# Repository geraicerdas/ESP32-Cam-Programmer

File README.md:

### Repository Content
* **/hardware** : Schematic files (.pdf) some of older version included Eagle design files (.sch and .brd)
* **/production** : gerber file for pcb manufacturing

You can purchase this product from  

# ESP32-Cam-Programmer
This is external programming for ESP32-Cam that you can simple attach it for easy upload your code to ESP32-Cam. Keep the slide switch at 3.3V so it is not harmful for your ESP32-Cam. ESP32-Cam programmer also have a breakout pins that makes it easier for you to connect the I/O pins of the ESP32-Cam to other circuits (no need breadboard). Not only for ESP32-Cam, you can use this board to program another MCU's like Arduino Pro mini that need USB to Serial Converter

The latest version have several changes :
- Added a 3V3 Voltage Regulator
- Added voltage selector switch (5V or 3.3V compatible)
- Compatible with both older or newer ESP32-Cam
- changes PCB shape and color

If you want to make your self, just download the gerber file in production folder. Send it to your fav pcb manufacturer. And dont forget to get the Bill of materials :
|Qty | Part Name | Parts | MPN |
| ------------- |:-------------|:-------------| -----:|
| 2 | Female Header 8P 2.54mm pitch | J5 | X6511FV-08-C85D32 |
| 2 | Male Header 8P 2.54mm pitch | J2, J3 | X4611WRS-08I-C40D28 |
| 1 | USB type C Connector 16P | J4 | U262-161N-4BVC11 |
| 1 | CH340G/CH340C | U1 | CH340G |
| 1 | SMD Resonator 12MHz CSTCE | X1 | CSTCE12M0G15C99-R0 |
| 1 | AP2112K-3.3TRG1 | U2 | AP2112K-3.3TRG1 |
| 1 | Chip Resistor 0 0805 | R10, R11 | 0805W8F0000T5E |
| 3 | Chip Resistor 1K 0603 | R4, R6, R7 | 0603WAF1001T5E |
| 3 | Chip Resistor 10K 0603 | R1, R2, R3 | 0603WAF1002T5E |
| 2 | Chip Resistor 4K7 0603 | R8, R9 | 0603WAF4701T5E |
| 5 | Chip Capacitor 100nF 0603 | C3, C5, C6, C8, C21 | CL10B104KB8NNNC |
| 3 | Chip Capacitor 10uF 0603 | C2, C4, C7 | CL10A106KP8NNNC |
| 1 | N-Channel MOSFET AO3400 | Q1 | AO3400 |
| 2 | Transistor S8050 | Q2, Q3 | S8050 |
| 2 | Slide Switch AYZ0202W | SW | SS-3390S-L2 |
| 2 | Push Button YD3414 | S1, S2 | TS-1186U-B-A |
| 2 | SMD LED 0805 Red | RX, TX | 17-21/R6C-AQ2R2B/3T |
| 1 | SMD LED 0805 Green | PWR | 17-21/GHC-YR1S2/3T |
| 1 | Schottky Diode 1N5819HW | D1 | 1N5819WS |

Below is the first version of ESP32-Cam Programmer. We keep this for your references.

## License
*We invests time and resources providing this open-source hardware, please support us by purchasing our products.*

*Designed by **[Insan Sains](https://www.youtube.com/insansains)** for **[Gerai Cerdas](https://geraicerdas.com)**, with contributions from the open source community. Creative Commons Attribution/Share-Alike, all text above must be included in any redistribution. See license.txt for additional information.*

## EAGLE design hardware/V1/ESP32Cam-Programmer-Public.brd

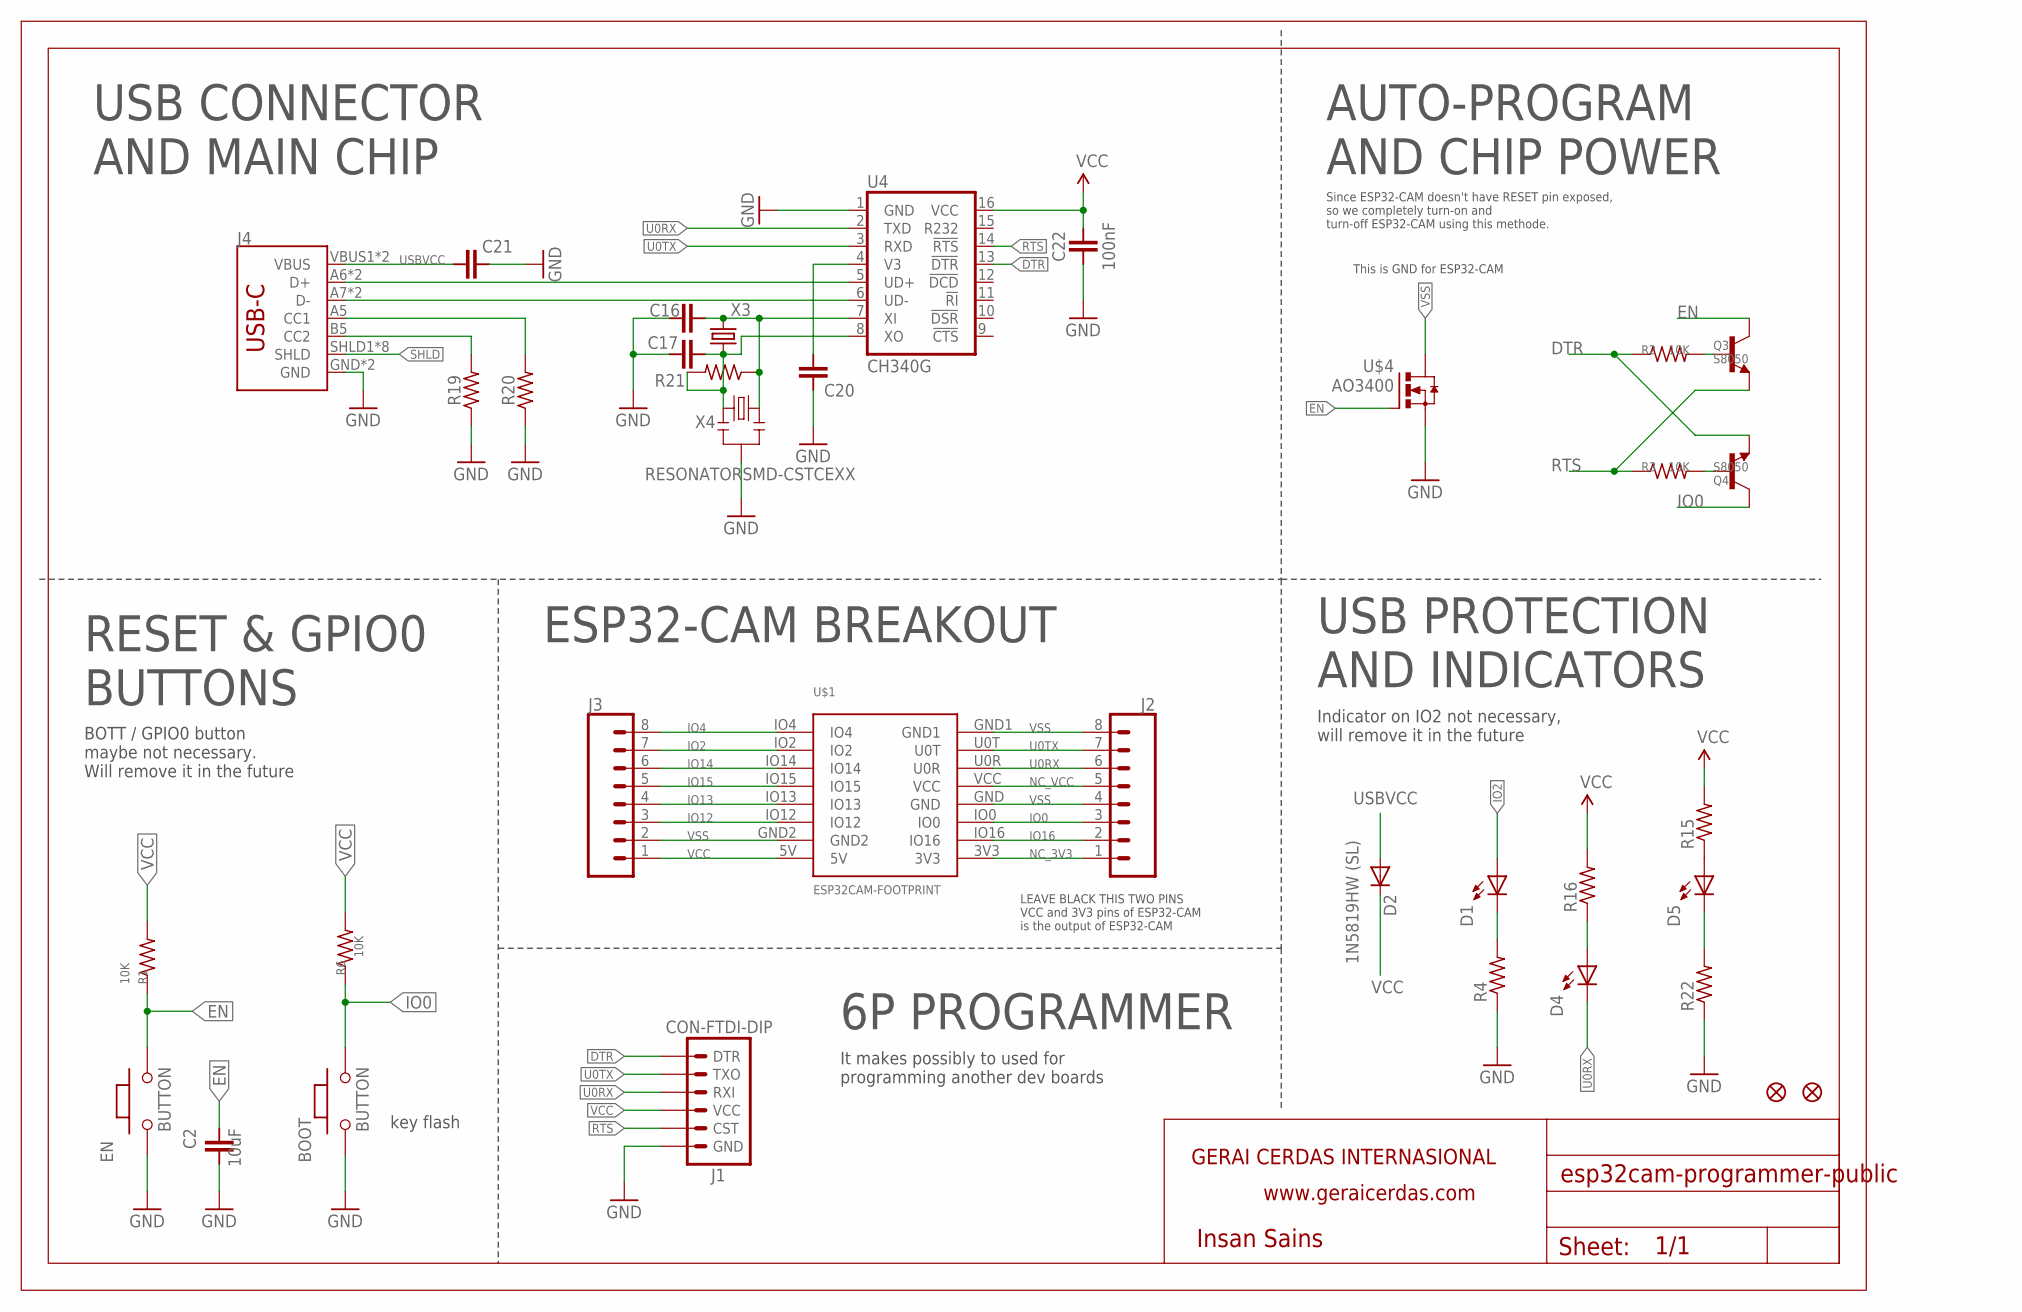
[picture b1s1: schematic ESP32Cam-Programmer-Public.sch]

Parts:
BOOT: BUTTON; 157SW
C2: 10uF; C0603
C16, C17: 10pF; C0603
C20: 10nF; C0603
C21, C22: 100nF; C0603
D1, D5: Yellow; LED0805
D2: 1N5819HW (SL); SOD-323
D4: GREEN; LED0805
EN: BUTTON; 157SW
J1: CON-FTDI-DIP; CON-FTDI
J2, J3: CONN_08"; 1X08
J4: USB_C16PIN; USB-C-16P
JP8, JP9: FIDUCIAL1X2; FIDUCIAL-1X2
Q3, Q4: S8050; SOT-23
R1, R2, R3, R6: 10K; R0603
R4, R22: 1K; R0603
R15, R16: 330; R0603
R19, R20: 5.1k; R0603
R21: RESISTOR-SMD0603; R0603
U4: CH340G; SO016
U$1: ESP32CAM-FOOTPRINT; ESP32CAM
U$4: AO3400; SOT-23
U$13: FRAME; A4-HOR
X3: XTAL-SMD; SMD-CRYSTAL
X4: RESONATORSMD-CSTCEXX; CSTCE*

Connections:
CC3: J4.A5 (CC1), R20.2
CC4: J4.B5 (CC2), R19.2
D+2: J4.A6 (D+), J4.B6 (D+), U4.5 (UD+)
D-2: J4.A7 (D-), J4.B7 (D-), U4.6 (UD-)
DTR: J1.DTR, Q4.2 (E), R2.1, U4.13 (!DTR)
EN: C2.2, EN.2, Q3.3 (C), R1.1, U$4.1 (G)
GND: BOOT.1, C2.1, C16.1, C17.1, C20.2, C21.2, C22.1, EN.1, J1.GND, J4.GND, J4.GND2 (GND), R4.1, R19.1, R20.1, R22.1, U4.1 (GND), U$4.2 (S), X4.2
IO0: BOOT.2, J2.3, Q4.3 (C), R6.1, U$1.IO0
IO2: D1.A, J3.7, U$1.IO2
IO4: J3.8, U$1.IO4
IO12: J3.3, U$1.IO12
IO13: J3.4, U$1.IO13
IO14: J3.6, U$1.IO14
IO15: J3.5, U$1.IO15
IO16: J2.2, U$1.IO16
unnamed: D1.C, R4.2
unnamed: Q3.1 (B), R2.2
unnamed: Q4.1 (B), R3.2
unnamed: D4.A, R16.1
unnamed: D5.A, R15.1
unnamed: C17.2, R21.2, U4.8 (XO), X3.1, X4.1
unnamed: C16.2, R21.1, U4.7 (XI), X3.2, X4.3
unnamed: D5.C, R22.2
NC_3V3: J2.1, U$1.3V3
NC_VCC: J2.5, U$1.VCC
RTS: J1.CTS (CST), Q3.2 (E), R3.1, U4.14 (!RTS)
SHLD: J4.SHLD1 (SHLD), J4.SHLD2 (SHLD), J4.SHLD3 (SHLD), J4.SHLD4 (SHLD), J4.SHLD5 (SHLD), J4.SHLD6 (SHLD), J4.SHLD7 (SHLD), J4.SHLD8 (SHLD)
U0RX: D4.C, J1.RXI, J2.6, U4.2 (TXD), U$1.U0R
U0TX: J1.TX0 (TXO), J2.7, U4.3 (RXD), U$1.U0T
USBVCC: C21.1, D2.A, J4.VBUS1 (VBUS), J4.VBUS2 (VBUS)
V1: C20.1, U4.4 (V3)
VCC: C22.2, D2.C, J1.VCC, J3.1, R1.2, R6.2, R15.2, R16.2, U4.16 (VCC), U$1.5V
VSS: J2.4, J2.8, J3.2, U$1.GND, U$1.GND1, U$1.GND2, U$4.3 (D)

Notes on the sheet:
Insan Sains
key flash
BOTT / GPIO0 button maybe not necessary. Will remove it in the future
This is GND for ESP32-CAM
LEAVE BLACK THIS TWO PINS VCC and 3V3 pins of ESP32-CAM is the output of ESP32-CAM
USB CONNECTOR AND MAIN CHIP
AUTO-PROGRAM AND CHIP POWER
USB PROTECTION AND INDICATORS
6P PROGRAMMER
ESP32-CAM BREAKOUT
RESET & GPIO0 BUTTONS
Indicator on IO2 not necessary, will remove it in the future
It makes possibly to used for programming another dev boards
Since ESP32-CAM doesn't have RESET pin exposed, so we completely turn-on and turn-off ESP32-CAM using this methode.

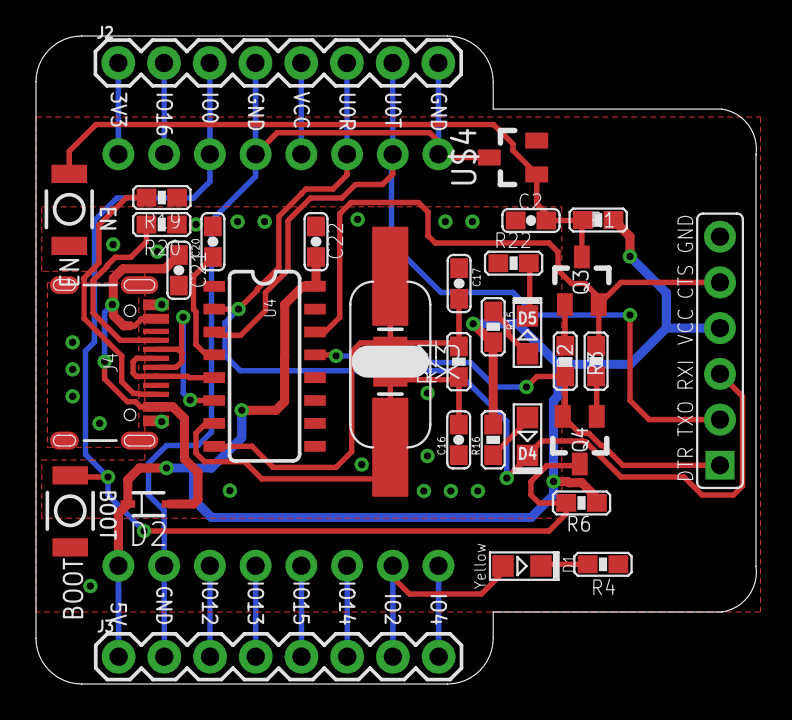
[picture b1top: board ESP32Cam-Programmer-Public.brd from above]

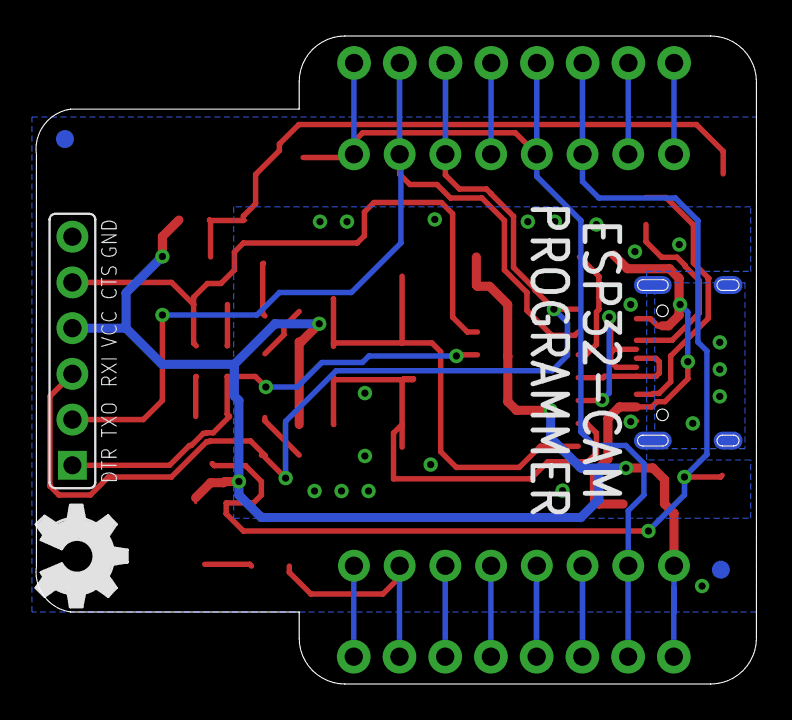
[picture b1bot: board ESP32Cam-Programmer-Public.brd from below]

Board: 2 copper layers, 40.0 x 36.0 mm, 38 parts (4 on the bottom side), 33 nets.

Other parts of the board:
U$2: OSHW_FILLX200_NOTEXT

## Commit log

2022-02-26 Rename hardware/ESP32Cam-Programmer-Public.brd to hardware/V1/ESP32Cam-Programmer-Public.brd
2022-02-26 Rename hardware/ESP32Cam-Programmer-Public.sch to hardware/V1/ESP32Cam-Programmer-Public.sch

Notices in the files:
parts and their libraries:
SparkFun-Aesthetics: Licensing: CC v3.0 Share-Alike You are welcome to use this library for commercial purposes.
SparkFun-DigitalIC: Licensing: Creative Commons ShareAlike 4.0 International - https://creativecommons.org/licenses/by-sa/4.0
